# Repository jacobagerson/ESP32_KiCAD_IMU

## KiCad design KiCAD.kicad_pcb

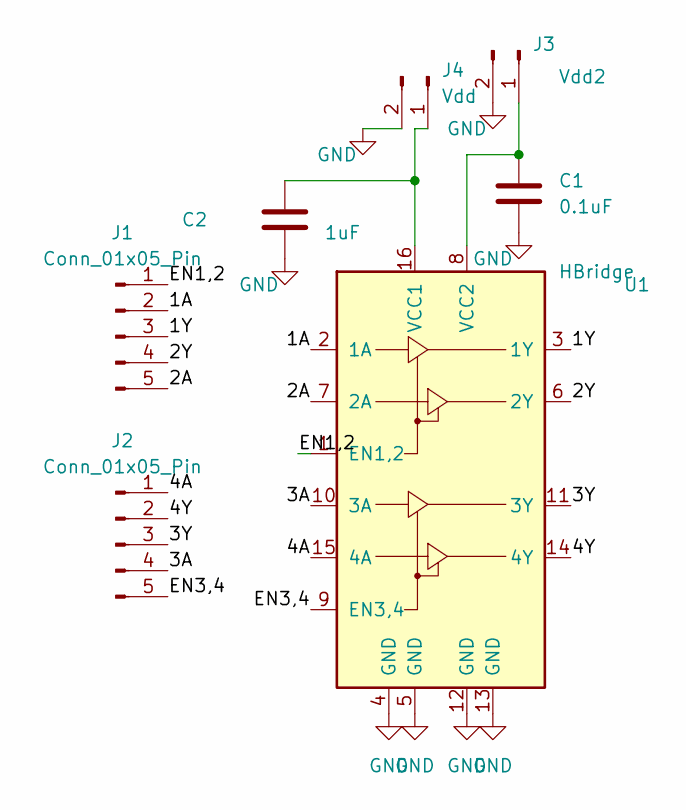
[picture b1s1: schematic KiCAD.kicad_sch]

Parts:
C1: 0.1uF; C_0805_2012Metric_Pad1.18x1.45mm_HandSolder
C2: 1uF; C_0805_2012Metric_Pad1.18x1.45mm_HandSolder
J1, J2: Conn_01x05_Pin; PinHeader_1x05_P2.54mm_Vertical
J3: Vdd2; PinHeader_1x02_P2.54mm_Vertical
J4: Vdd; PinHeader_1x02_P2.54mm_Vertical
U1: HBridge; DIP-16_W7.62mm

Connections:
/1A: J1.2, U1.2 (1A)
/1Y: J1.3, U1.3 (1Y)
/2A: J1.5, U1.7 (2A)
/2Y: J1.4, U1.6 (2Y)
/3A: J2.4, U1.10 (3A)
/3Y: J2.3, U1.11 (3Y)
/4A: J2.1, U1.15 (4A)
/4Y: J2.2, U1.14 (4Y)
/EN1,2: J1.1, U1.1 (EN1,2)
/EN3,4: J2.5, U1.9 (EN3,4)
GND: C1.2, C2.2, J3.2, J4.2, U1.4 (GND), U1.5 (GND), U1.12 (GND), U1.13 (GND)
unnamed: C1.1, J3.1, U1.8 (VCC2)
unnamed: C2.1, J4.1, U1.16 (VCC1)

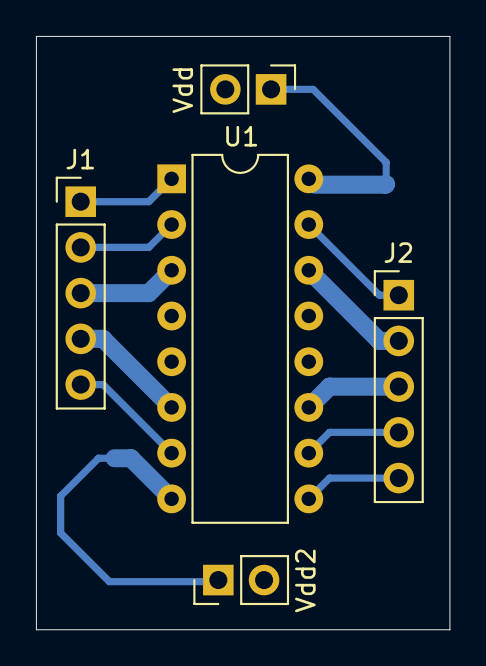
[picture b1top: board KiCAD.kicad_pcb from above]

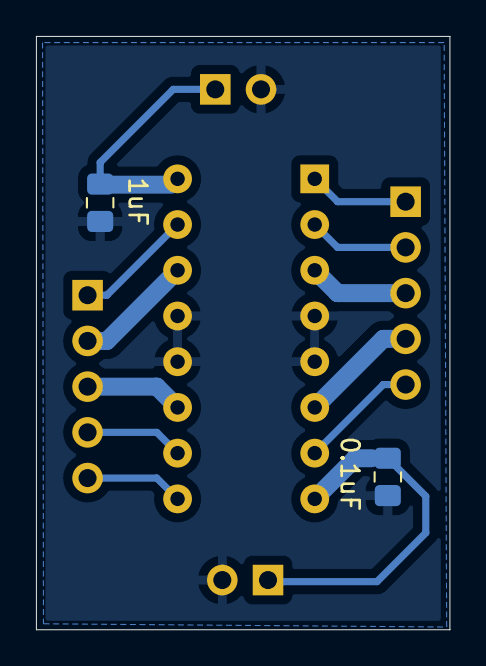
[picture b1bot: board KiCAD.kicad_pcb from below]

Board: 2 copper layers, 23.0 x 33.0 mm, 7 parts (2 on the bottom side), 13 nets.

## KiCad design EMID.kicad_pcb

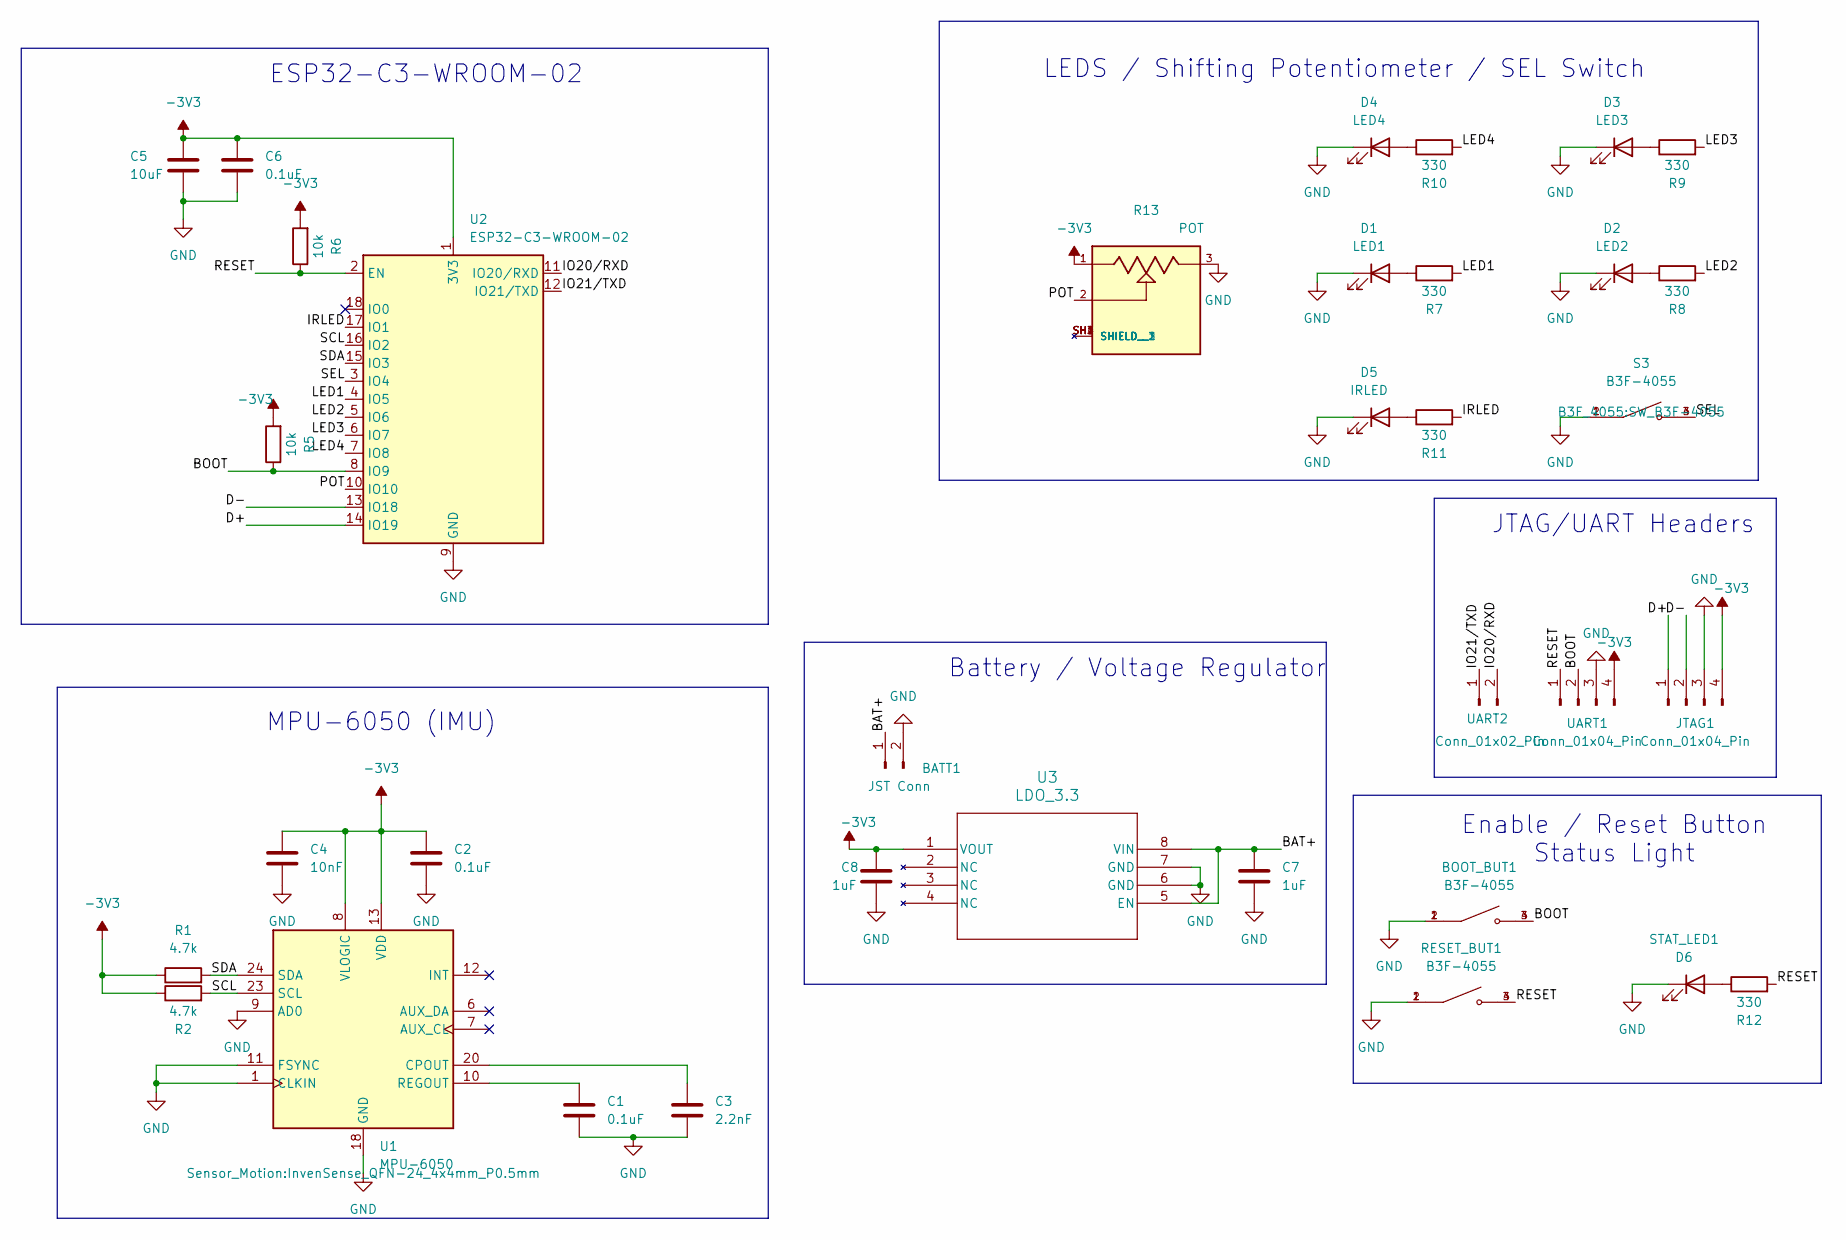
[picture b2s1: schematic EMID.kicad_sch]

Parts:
BATT1: JST Conn; JST_EH_B2B-EH-A_1x02_P2.50mm_Vertical
BOOT_BUT1: B3F-4055; SW_B3F-4055; PARTREV A070-E1-08
C1, C2, C6: 0.1uF; C_0805_2012Metric_Pad1.18x1.45mm_HandSolder
C3: 2.2nF; C_0805_2012Metric_Pad1.18x1.45mm_HandSolder
C4: 10nF; C_0805_2012Metric_Pad1.18x1.45mm_HandSolder
C5: 10uF; C_0805_2012Metric_Pad1.18x1.45mm_HandSolder
C7, C8: 1uF; C_0805_2012Metric_Pad1.18x1.45mm_HandSolder
D1: LED1; LED_D3.0mm
D2: LED2; LED_D3.0mm
D3: LED3; LED_D3.0mm
D4: LED4; LED_D3.0mm
D5: IRLED; LED_D3.0mm
JTAG1: Conn_01x04_Pin; PinHeader_1x04_P2.54mm_Vertical
R1, R2: 4.7k; R_0805_2012Metric_Pad1.20x1.40mm_HandSolder
R5, R6: 10k; R_0805_2012Metric_Pad1.20x1.40mm_HandSolder
R7, R8, R9, R10, R11, R12: 330; R_0805_2012Metric_Pad1.20x1.40mm_HandSolder
R13: POT; TRIM_PTA4543-2015CPB104; PARTREV 04/21
RESET_BUT1: B3F-4055; SW_B3F-4055; PARTREV A070-E1-08
S3: B3F-4055; SW_B3F-4055; PARTREV A070-E1-08
STAT_LED1: D6; LED_0805_2012Metric_Pad1.15x1.40mm_HandSolder
U1: MPU-6050; InvenSense_QFN-24_4x4mm_P0.5mm
U2: ESP32-C3-WROOM-02
U3: LDO_3.3; AP2112M-3.3TRG1_DIO
UART1: Conn_01x04_Pin; PinHeader_1x04_P2.54mm_Vertical
UART2: Conn_01x02_Pin; PinHeader_1x02_P2.54mm_Vertical

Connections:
-3V3: C2.1, C4.1, C5.1, C6.1, C8.1, JTAG1.4, R1.1, R2.1, R5.2, R6.2, R13.1, U1.8 (VLOGIC), U1.13 (VDD), U2.1 (3V3), U3.1 (VOUT), UART1.4
/BAT+: BATT1.1, C7.1, U3.5 (EN), U3.8 (VIN)
/BOOT: BOOT_BUT1.3, BOOT_BUT1.4, R5.1, U2.8 (IO9), UART1.2
/D+: JTAG1.1, U2.14 (IO19)
/D-: JTAG1.2, U2.13 (IO18)
/IO20/RXD: U2.11 (IO20/RXD), UART2.2
/IO21/TXD: U2.12 (IO21/TXD), UART2.1
/IRLED: R11.2, U2.17 (IO1)
/LED1: R7.2, U2.4 (IO5)
/LED2: R8.2, U2.5 (IO6)
/LED3: R9.2, U2.6 (IO7)
/LED4: R10.2, U2.7 (IO8)
/POT: R13.2, U2.10 (IO10)
/RESET: R6.1, R12.2, RESET_BUT1.3, RESET_BUT1.4, U2.2 (EN), UART1.1
/SCL: R2.2, U1.23 (SCL), U2.16 (IO2)
/SDA: R1.2, U1.24 (SDA), U2.15 (IO3)
/SEL: S3.3, S3.4, U2.3 (IO4)
GND: BATT1.2, BOOT_BUT1.1, BOOT_BUT1.2, C1.2, C2.2, C3.2, C4.2, C5.2, C6.2, C7.2, C8.2, D1.1 (K), D2.1 (K), D3.1 (K), D4.1 (K), D5.1 (K), JTAG1.3, R13.3, RESET_BUT1.1, RESET_BUT1.2, S3.1, S3.2, STAT_LED1.1 (K), U1.1 (CLKIN), U1.9 (AD0), U1.11 (FSYNC), U1.18 (GND), U2.9 (GND), U2.19 (GND), U3.6 (GND), U3.7 (GND), UART1.3; also elsewhere on the board
unnamed: D1.2 (A), R7.1
unnamed: D2.2 (A), R8.1
unnamed: D3.2 (A), R9.1
unnamed: D4.2 (A), R10.1
unnamed: D5.2 (A), R11.1
unnamed 23: R12.1, STAT_LED1.2 (A); also elsewhere on the board
unnamed: C3.1, U1.20 (CPOUT)
unnamed: C1.1, U1.10 (REGOUT)

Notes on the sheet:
Enable / Reset Button Status Light
LEDS / Shifting Potentiometer / SEL Switch
Battery / Voltage Regulator
ESP32-C3-WROOM-02
JTAG/UART Headers
MPU-6050 (IMU)

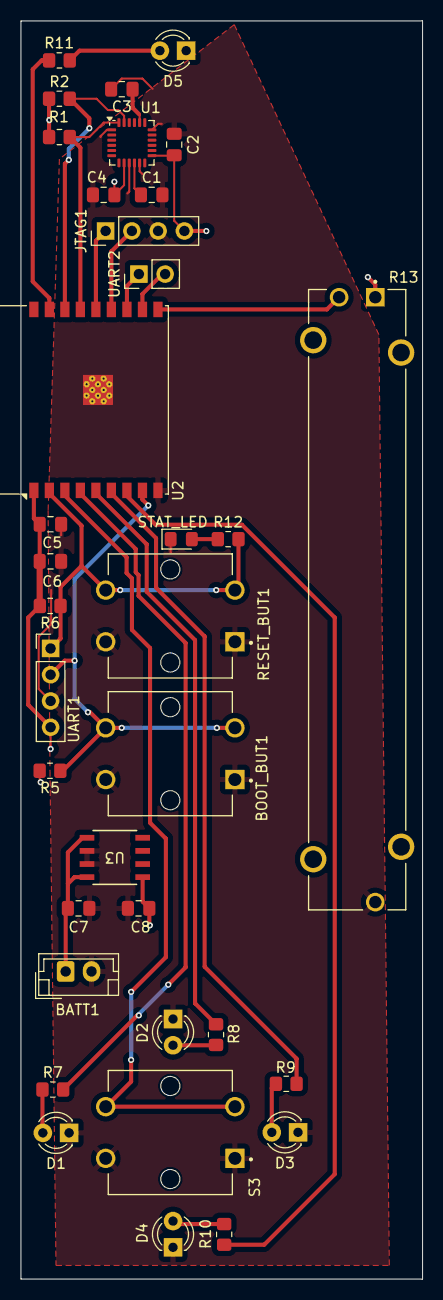
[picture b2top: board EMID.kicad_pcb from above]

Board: 2 copper layers, 38.8 x 121.7 mm, 35 parts (0 on the bottom side), 26 nets.

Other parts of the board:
STAT_LED: D6; LED_0805_2012Metric_Pad1.15x1.40mm_HandSolder

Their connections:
GND: STAT_LED.1 (K); also elsewhere on the board
unnamed 23: STAT_LED.2 (A); also elsewhere on the board

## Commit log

2025-12-16 12/15
2025-12-16 Final software update
2025-12-16 Hardware Upload
